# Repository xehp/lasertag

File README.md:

# lasertag
Laser tag toys, hardware and software.

The plan is to make some laser tag (but actually its IR that caries the signal) toys here.

It will avoid cables between pointer and vest/helmet for a better user experience and less maintenance.

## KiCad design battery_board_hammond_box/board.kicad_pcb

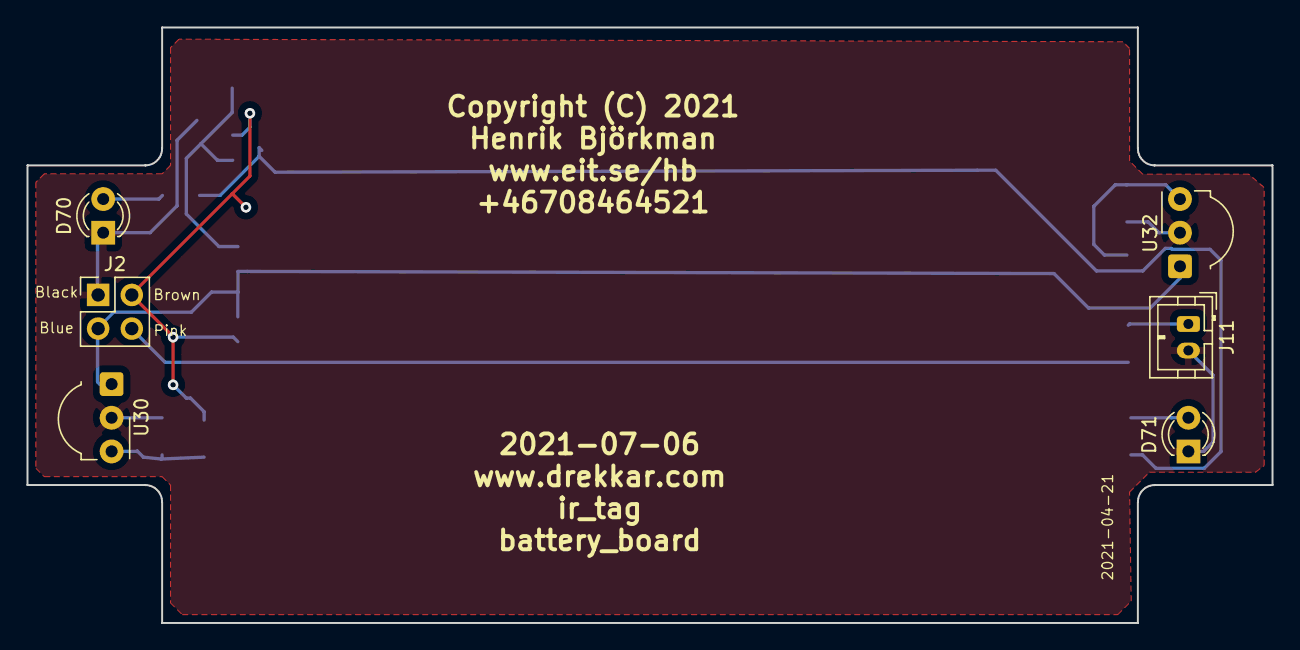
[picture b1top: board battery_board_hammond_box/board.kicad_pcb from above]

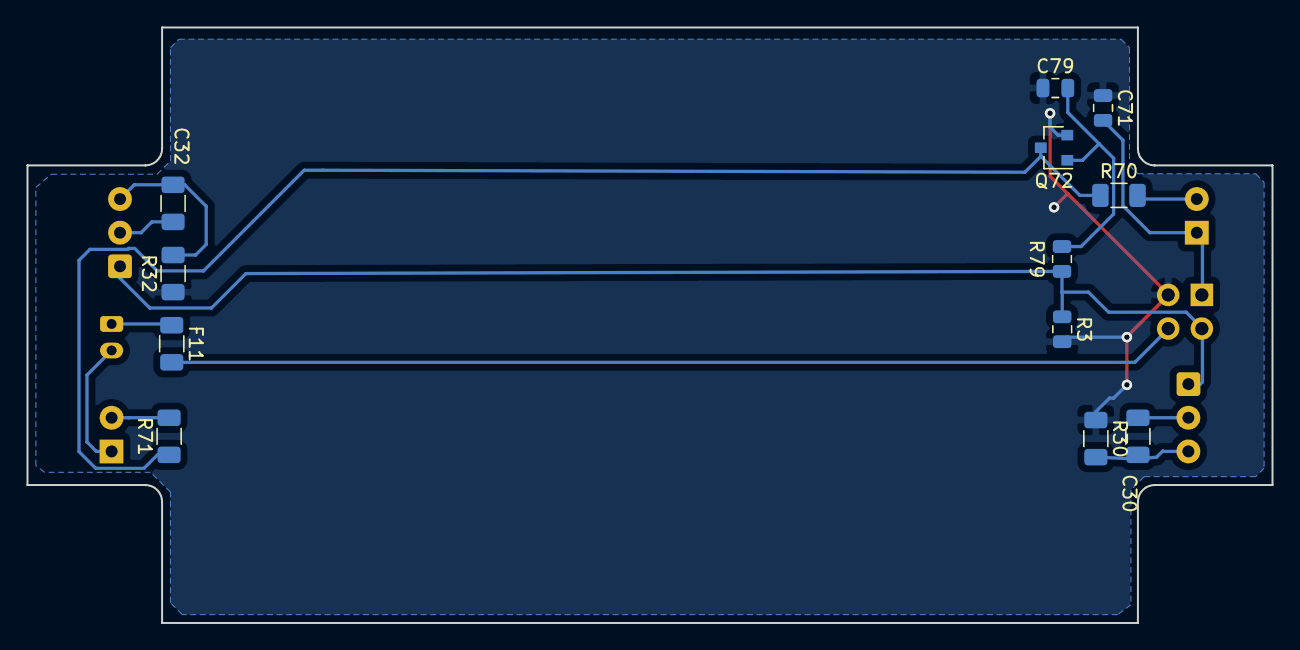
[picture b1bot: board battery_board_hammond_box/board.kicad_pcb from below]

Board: 2 copper layers, 94.0 x 45.0 mm, 18 parts (12 on the bottom side), 11 nets.

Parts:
C30, C32: 10uF; C_1206_3216Metric
C71: 1uF; C_0805_2012Metric
C79: 10nF; C_0805_2012Metric
D70, D71: red; LED_D3.0mm
F11: Fuse; R_1206_3216Metric
J2: Conn_01x04-Connector_Generic; PinHeader_2x02_P2.54mm_Vertical
J11: Conn_01x02; JST_PH_B2B-PH-K_1x02_P2.00mm_Vertical
Q72: Q_PMOS_GSD; SOT-23
R3, R79: 10K; R_0805_2012Metric
R30, R32, R70, R71: 10; R_1206_3216Metric
U30, U32: TSOP34S40F; Vishay_MOLD-3Pin

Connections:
GND: C30.2, C32.2, C71.2, D70.1, D71.1, J2.1, J11.2, U30.2, U32.2
unnamed: C30.1, R30.2, U30.3
unnamed: C32.1, R32.2, U32.3
unnamed: C79.2, Q72.1, R79.1
unnamed: D70.2, R70.2
unnamed: D71.2, R71.2
unnamed: F11.1, J11.1
unnamed: F11.2, J2.4
unnamed: J2.3, R3.1, R79.2, U30.1, U32.1
unnamed: Q72.3, R70.1, R71.1
VCC: C71.1, C79.1, J2.2, Q72.2, R3.2, R30.1, R32.1

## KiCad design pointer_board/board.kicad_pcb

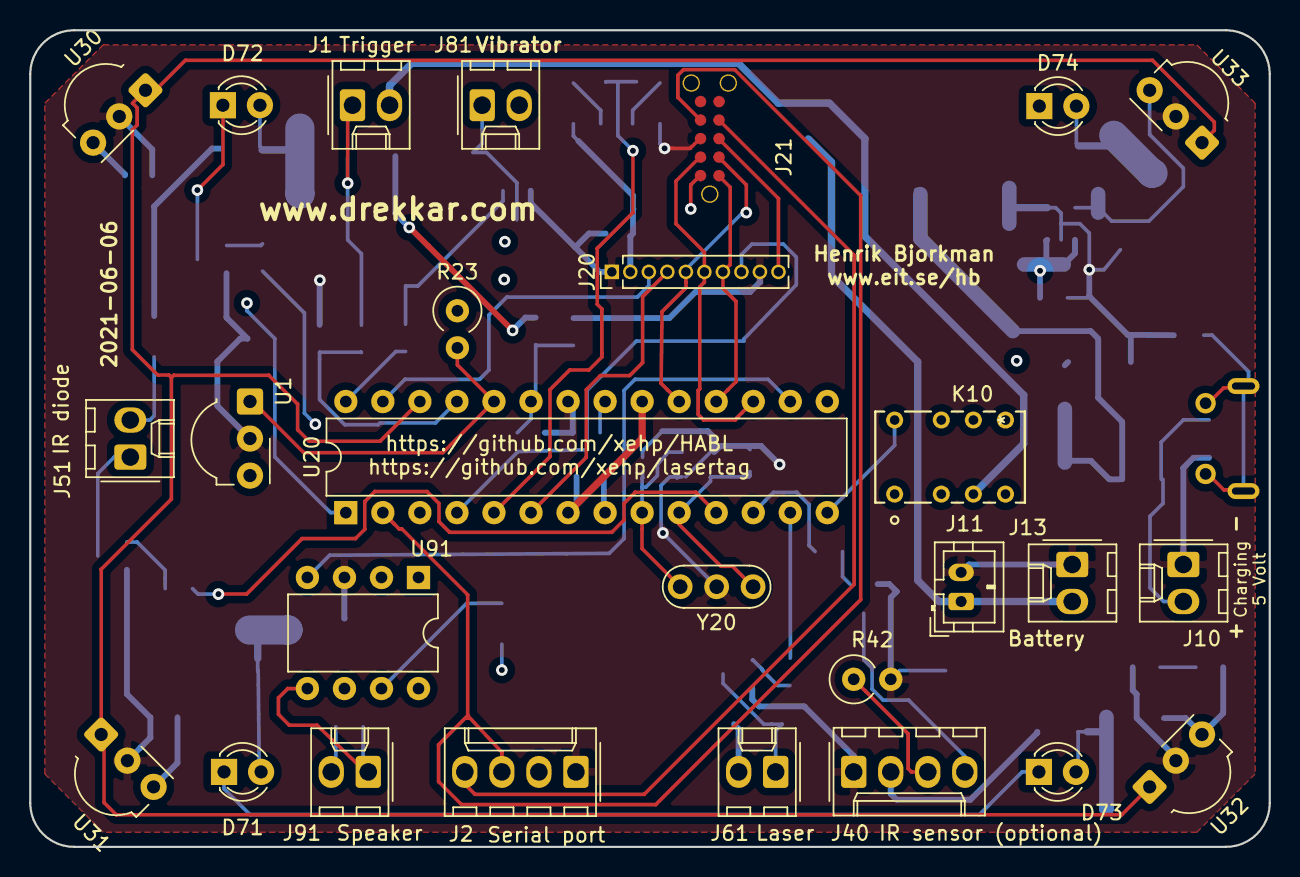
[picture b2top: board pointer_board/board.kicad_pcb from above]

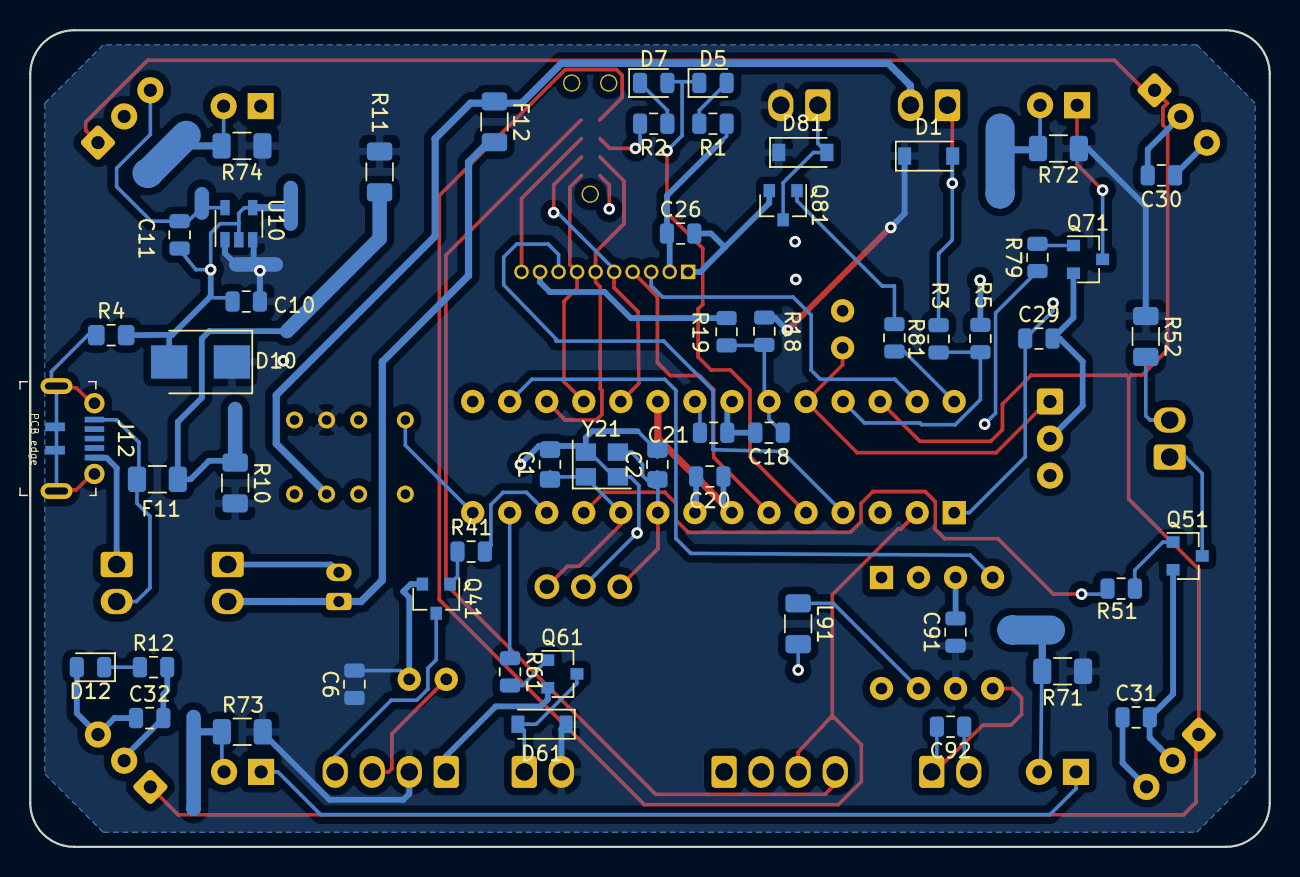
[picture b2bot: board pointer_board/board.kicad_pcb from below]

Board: 4 copper layers, 85.0 x 56.0 mm, 80 parts (53 on the bottom side), 55 nets.

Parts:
C1, C2: 10 pF; C_0805_2012Metric_Pad1.15x1.40mm_HandSolder
C6, C26: 10uF; C_0805_2012Metric
C10, C11, C18, C92: 1uF; C_0805_2012Metric
C20, C21, C29, C30, C31, C32, C91: 0.1uF; C_0805_2012Metric
D1, D61, D81: D; D_SOD-123
D5: yellow or amber; LED_0805_2012Metric
D7: green or blue; LED_0805_2012Metric
D10: D_Zener; D_SMB
D12: red; LED_0805_2012Metric
D71, D72, D73, D74: red; LED_D3.0mm
F11, F12: Fuse; R_1206_3216Metric
J1, J10, J13, J51, J61, J81, J91: Conn_01x02; Molex_KK-254_AE-6410-02A_1x02_P2.54mm_Vertical
J2, J40: Conn_01x04; Molex_KK-254_AE-6410-04A_1x04_P2.54mm_Vertical
J11: Conn_01x02; JST_PH_B2B-PH-K_1x02_P2.00mm_Vertical
J12: USB_B_Micro; USB_Micro_B_Female_jlcpcb
J20: Conn_01x10; PinHeader_1x10_P1.27mm_Vertical
J21: connector_10pin_ISP_Console; connector_10pin_TC2050-IDC-NL
K10: 1-1462039-5
L91: 10uH; L_1206_3216Metric
Q41, Q51, Q61, Q71, Q81: S8050; SOT-23
R1, R2, R12, R41, R51, R61, R79, R81: 100; R_0805_2012Metric
R3: 3.3K; R_0805_2012Metric
R4: 27; R_0805_2012Metric_Pad1.15x1.40mm_HandSolder
R5, R19: 10K; R_0805_2012Metric
R10, R11, R71, R72, R73, R74: 10; R_1206_3216Metric
R18: 47K; R_0805_2012Metric
R23: 10K; R_Axial_DIN0309_L9.0mm_D3.2mm_P2.54mm_Vertical
R42: 22K; R_Axial_DIN0309_L9.0mm_D3.2mm_P2.54mm_Vertical
R52: 3.3; R_1206_3216Metric
U1, U30, U31, U32, U33: TSOP34S40F; Vishay_MOLD-3Pin
U10: Low_dropout_regulator_TPS782; SOT-23-5
U20: ATmega328-PU; DIP-28_W7.62mm
U91: EL7202CN; DIP-8_W7.62mm
Y20: Crystal_GND2; Resonator-3Pin_W7.0mm_H2.5mm
Y21: Crystal_GND24; Crystal_SMD_3225-4Pin_3.2x2.5mm

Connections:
+3V3: C11.1, C20.1, C26.1, C30.1, C31.1, C32.1, D12.2, J2.2, J20.2, J21.2, K10.1, R1.1, R23.1, U1.3, U10.5, U20.7, U20.20, U30.3, U31.3, U32.3, U33.3
+BATT: C6.1, C10.1, C91.1, D1.1, D10.1, D61.1, D81.1, J40.2, J61.2, J81.2, K10.6, R10.2, R11.2, R18.1, R52.1, R71.1, R72.1, R73.1, R74.1, U10.1, U10.3, U91.6
/MISO: J20.7, J21.1, U20.18
/MOSI: J20.6, J21.4, U20.17
/PD0: J2.3, J21.8, U20.2
/PD1: J2.4, J21.7, U20.3
/Reset_: C29.1, J20.10, J21.5, U20.1
/SCK: J20.5, J21.3, U20.19
GND: C1.2, C2.2, C6.2, C10.2, C11.2, C18.2, C20.2, C21.2, C26.2, C29.2, C30.2, C31.2, C32.2, C91.2, D10.2, J2.1, J10.1, J11.2, J12.5, J13.1, J20.1, J20.9, J21.6, J40.1, Q41.2, Q51.2, Q61.2, Q71.2, Q81.2, R2.2, R4.2, R5.2, R12.2, R19.2, R42.2, U1.2, U10.2, U10.4, U20.8, U20.22, U30.2, U31.2, U32.2, U33.2, U91.3, Y20.2, Y21.2, Y21.4
unnamed: C1.1, U20.10, Y20.1, Y21.1
unnamed: C2.1, U20.9, Y20.3, Y21.3
unnamed: C18.1, R18.2, R19.1, U20.23
unnamed: C21.1, U20.21
unnamed: C92.1, J91.2, L91.2
unnamed: C92.2, J91.1, U91.5
unnamed: D1.2, J1.1, R3.1
unnamed: D5.1, D7.2, U20.5
unnamed: D5.2, R1.2
unnamed: D7.1, R2.1
unnamed: D12.1, R12.1
unnamed: D61.2, J61.1, Q61.3
unnamed: D71.1, D72.1, D73.1, D74.1, Q71.3
unnamed: D71.2, R71.2
unnamed: D72.2, R72.2
unnamed: D73.2, R73.2
unnamed: D74.2, R74.2
unnamed: D81.2, J81.1, Q81.3
unnamed: F11.1, J10.2, J12.1
unnamed: F11.2, R10.1, R11.1
unnamed: F12.1, J1.2, K10.3
unnamed: F12.2, J11.1, J13.2
unnamed: J12.6, R4.1
unnamed: J20.3, U20.27
unnamed: J20.4, U20.6
unnamed: J20.8, U20.4
unnamed: J40.3, R23.2, R42.1, U1.1, U20.24
unnamed: J40.4, Q41.3
unnamed: J51.1, Q51.3
unnamed: J51.2, R52.2
unnamed: K10.4, K10.5
unnamed: K10.8, U20.14
unnamed: L91.1, U91.7
unnamed: Q41.1, R41.1
unnamed: Q51.1, R51.2
unnamed: Q61.1, R61.2
unnamed: Q71.1, R79.2
unnamed: Q81.1, R81.2
unnamed: R3.2, R5.1, U20.25
unnamed: R41.2, R79.1, U20.12
unnamed: R51.1, U20.11
unnamed: R61.1, U20.13
unnamed: R81.1, U20.28
unnamed: U20.15, U91.2
unnamed: U20.16, U91.4
unnamed: U20.26, U30.1, U31.1, U32.1, U33.1

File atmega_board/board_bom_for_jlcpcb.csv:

Comment,Designator,Footprint,LCSC
"1uF","C10,C11,C18,C92","Capacitor_SMD:C_0805_2012Metric",""
"0.1uF","C20,C21,C26,C29,C30,C31,C32,C91","Capacitor_SMD:C_0805_2012Metric",""
"D_Zener","D10","Diode_SMD:D_SMB",""
"red","D12,D71,D72,D73,D74","LED_THT:LED_D3.0mm",""
"yellow or amber","D5","LED_THT:LED_D3.0mm",""
"D","D1,D61,D81","Diode_SMD:D_SOD-123",""
"green or blue","D7","LED_THT:LED_D3.0mm",""
"Fuse","F11,F12","eit_footprints:Varistor_RV_Disc_D9mm_W5.7mm_P5mm",""
"Conn_01x02","J11","Connector_JST:JST_PH_B2B-PH-K_1x02_P2.00mm_Vertical",""
"USB_B_Micro","J12","Connector_USB:USB_Micro-B_Molex-105017-0001",""
"Conn_01x04","J2,J40","Connector_Molex:Molex_KK-254_AE-6410-04A_1x04_P2.54mm_Vertical",""
"Conn_01x10","J20","Connector_PinHeader_1.27mm:PinHeader_1x10_P1.27mm_Vertical",""
"Conn_01x02","J1,J10,J13,J51,J61,J81,J91","Connector_Molex:Molex_KK-254_AE-6410-02A_1x02_P2.54mm_Vertical",""
"1-1462039-5","K10","2021-04-01_19-01-27_footprints:1-1462039-5",""
"10uH","L91","Inductor_THT:L_Axial_L14.0mm_D4.5mm_P5.08mm_Vertical_Fastron_LACC",""
"BC817","Q41,Q51,Q61,Q71,Q81","Package_TO_SOT_SMD:SOT-23",""
"4.7 Ohm, >=3 W","R10","Resistor_THT:R_Axial_DIN0414_L11.9mm_D4.5mm_P5.08mm_Vertical",""
"47K","R18","Resistor_SMD:R_0805_2012Metric",""
"10K","R5,R19","Resistor_SMD:R_0805_2012Metric",""
"10K","R23","Resistor_THT:R_Axial_DIN0309_L9.0mm_D3.2mm_P2.54mm_Vertical",""
"3.3K","R3","Resistor_SMD:R_0805_2012Metric",""
"27","R4","Resistor_SMD:R_0805_2012Metric_Pad1.15x1.40mm_HandSolder",""
"22K","R42","Resistor_THT:R_Axial_DIN0309_L9.0mm_D3.2mm_P2.54mm_Vertical",""
"100","R41,R51,R61,R79,R81","Resistor_SMD:R_0805_2012Metric",""
"10","R71,R72,R73,R74","Resistor_SMD:R_1206_3216Metric",""
"MCP1825S","U10","eit_footprints:TO-220-3_with_heatsink_V8508B",""
"ATmega328-PU","U20","Package_DIP:DIP-28_W7.62mm",""
"TSOP34S40F","U1,U30,U31,U32,U33","OptoDevice:Vishay_MOLD-3Pin",""
"EL7202CN","U91","Package_DIP:DIP-8_W7.62mm",""
"Crystal_GND2","Y20","Crystal:Resonator-3Pin_W7.0mm_H2.5mm",""

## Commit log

2021-04-28 added files
2021-05-01 software updates
2021-05-01 found and fixed a bug in avr_spi_init
2021-05-01 Added CMD
2021-05-01 added safety_information_lithium_ion_batteries.txt
2021-05-02 added avr_eeprom
2021-05-11 many SW updates
2021-05-12 improved baudrate setting
2021-05-21 improved misc drivers
2021-05-21 schematics_2021-04-27_v5.1
2021-06-10 schematics_2021-05-27
2021-06-27 updated SW
2021-10-06 many changes
2021-11-04 exponential moving average (EMA)
2021-11-14 moved files to sub folders (sw, kicad, openscad)

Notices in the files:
battery_board_hammond_box/board.kicad_pcb:
Copyright (C) 2021
parts and their libraries:
Copyright 2016 Accelerated Designs. All rights reserved.
